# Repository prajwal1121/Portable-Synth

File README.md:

# Portable Synth
### An OP-1 inspired portable groovebox based around Teensy 4.1
Built using the awesome Teensy Audio Library
 
This project is still in progress, and will be for a while. Check back often for updates and bug fixes

**Current Status (1/13/2021)::white_check_mark:**

**Latest Updates (2/3/2021):** This code is outgrowing the Arduino IDE and I'm finally making the switch to VSCode and Platformio! This means the code will now and henceforth be organized in a more traditional C++ project structure rather than an awkward collections of .ino files. More importantly, the latest groovebox firmware has been reorganized into classes and multiple files in an effort to make it more modulualr and OOP-y. See README in Software folder for more information.

##### Check out the following links for development updates and more information about how to use the project files above
* Part 1 (Version 1): http://praj.tech/portfolio/portable-synth-v1-prototype/
* Part 2 (Version 1): http://praj.tech/portfolio/portable-synth-concept-design/
* Part 3 (Version 2): http://praj.tech/portfolio/porable-synth-hardware-upgrade/
* Part 4 (Version 2): http://praj.tech/portfolio/portable-synth-v2/

##### Or watch the demo videos here
###### V2
* Audio Recording and FM Radio: https://youtu.be/2ahzlKvuJ6E
* Build: https://youtu.be/Mdk-aUEtNno
* Sample Packs and Step Sequencer: https://youtu.be/XyqohSevqoo
* V2 Hardware and Synth with Mod Matrix: https://youtu.be/yj9AeDa9qw8

###### V1
* Endless Sequencer: https://youtu.be/U5Ci-TUZ0MY
* Recording and Sampling: https://youtu.be/KuPWz8McP5k
* Subtractive Synthesizer: https://youtu.be/QcZ3WIZ24l4

#### V2 - November 2020

#### V1 Prototype - August 2020

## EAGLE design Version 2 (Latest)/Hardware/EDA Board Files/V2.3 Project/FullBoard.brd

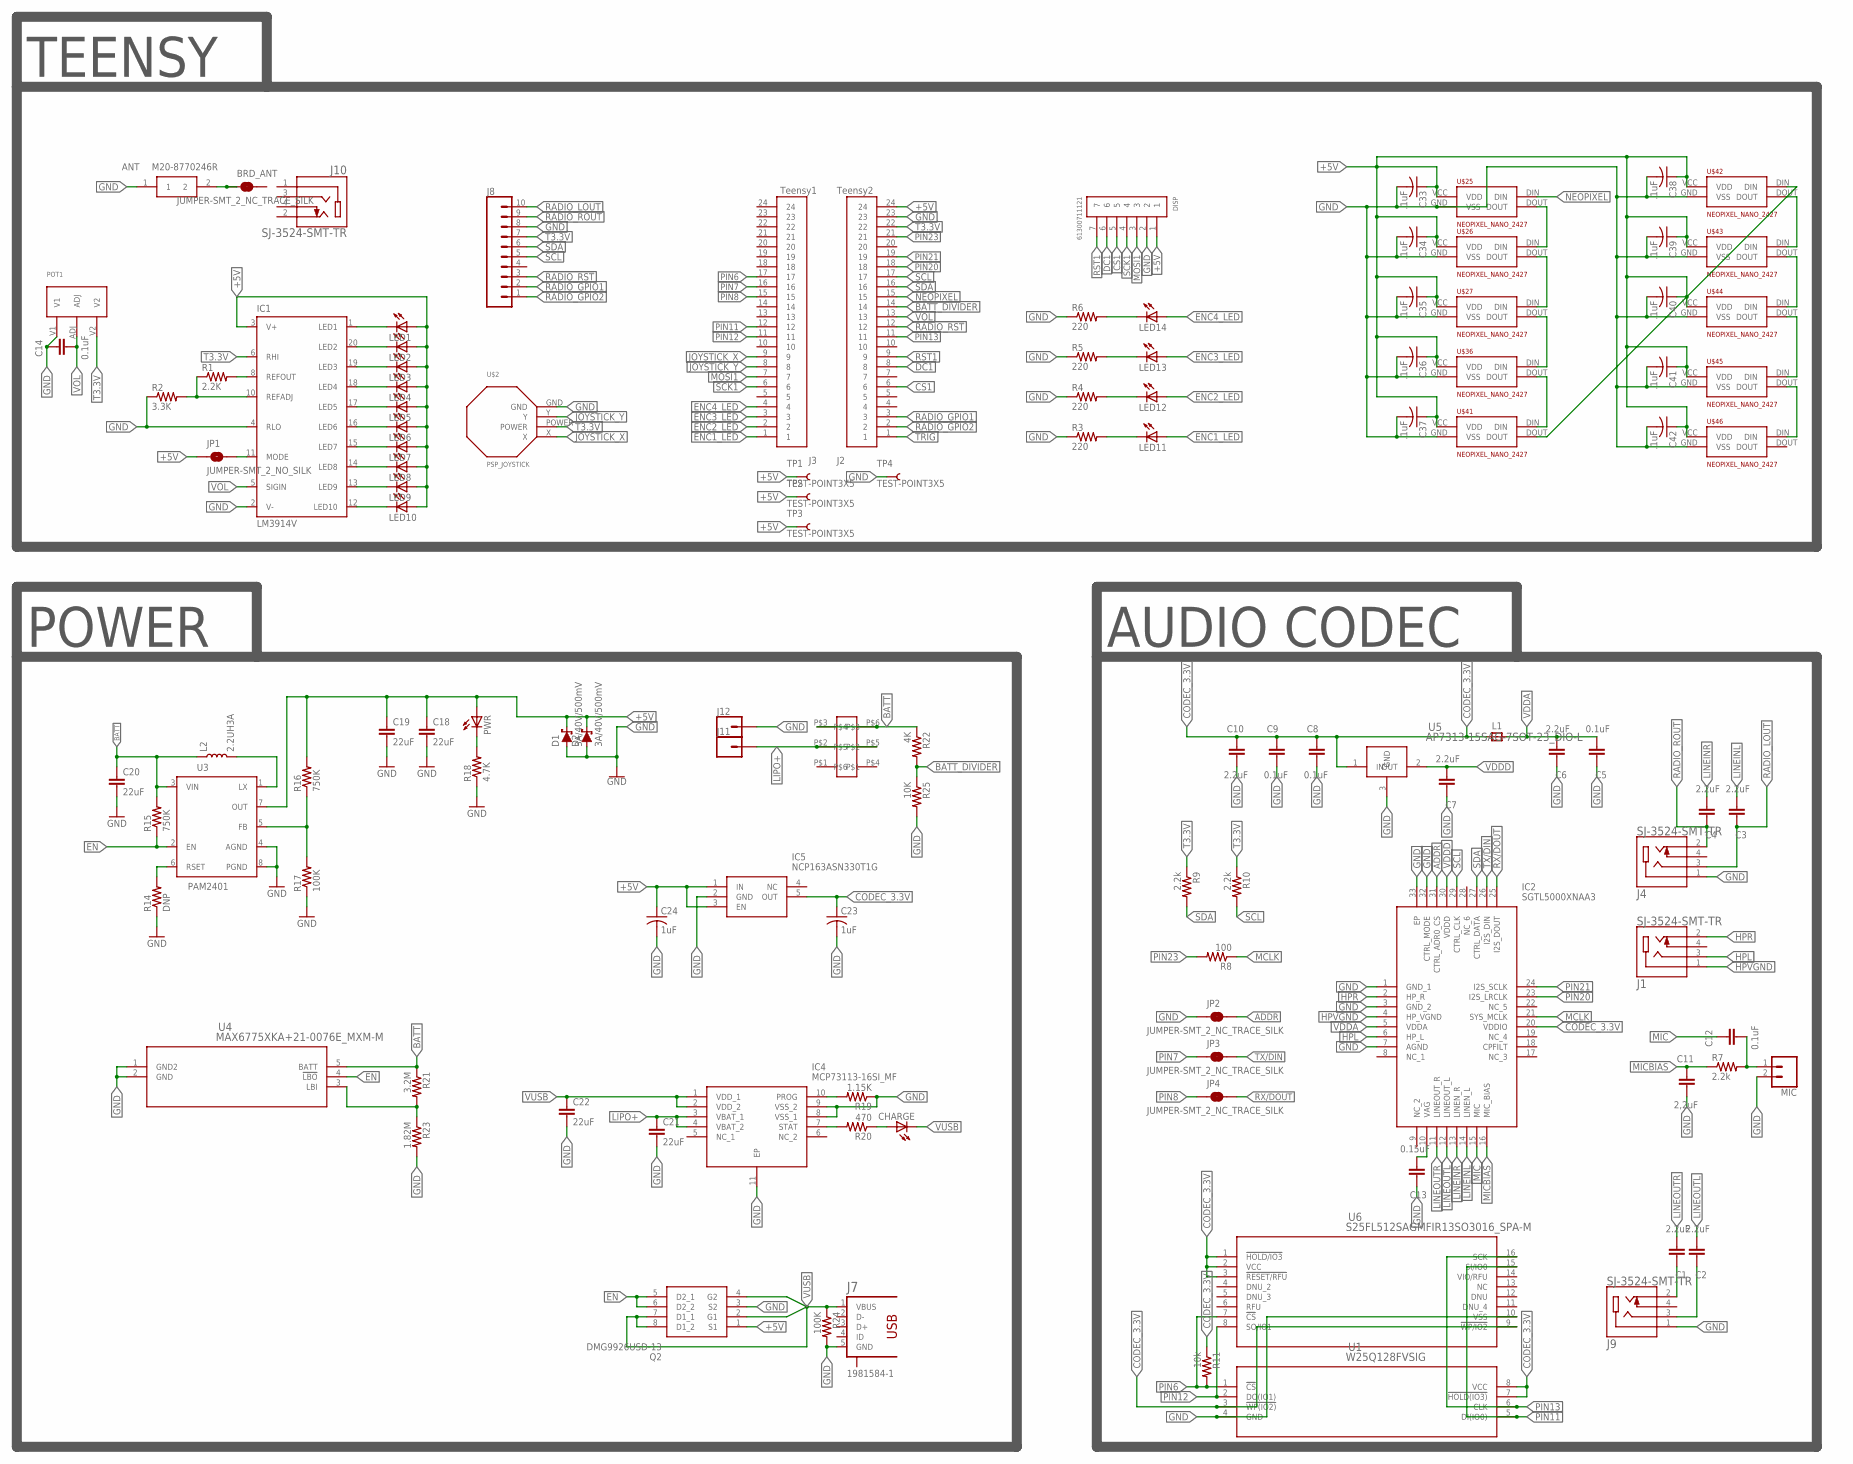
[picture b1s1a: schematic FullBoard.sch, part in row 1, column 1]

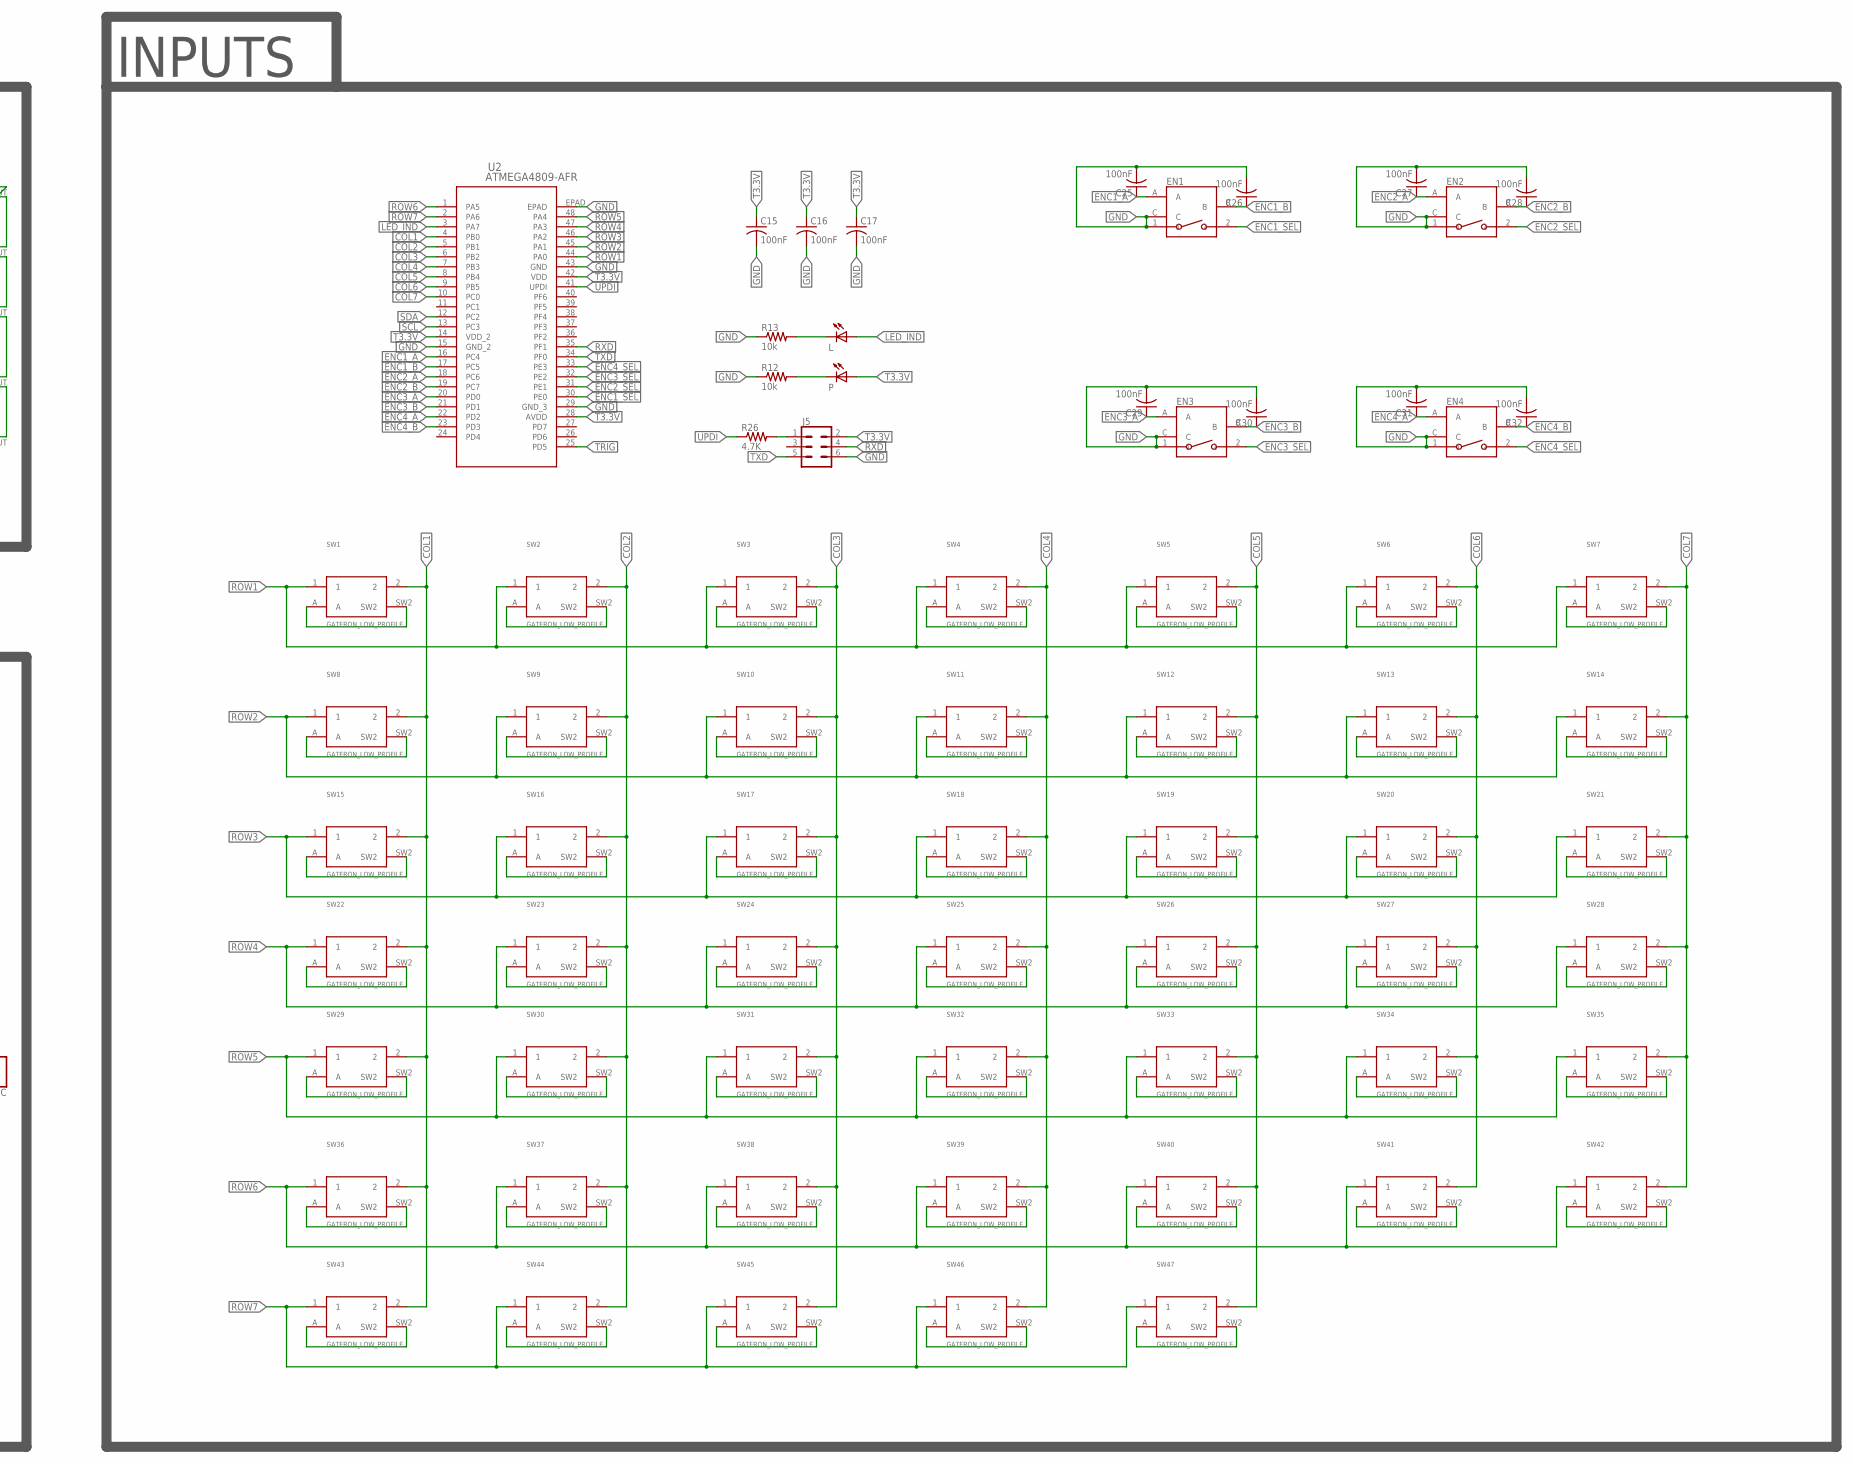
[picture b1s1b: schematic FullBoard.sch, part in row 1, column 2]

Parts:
ANT: M20-8770246R; M208770246R
BRD_ANT: JUMPER-SMT_2_NC_TRACE_SILK; SMT-JUMPER_2_NC_TRACE_SILK
C1, C2, C3, C4, C6, C7, C10: 2.2uF; CAP_0805
C5, C8, C9, C12, C14: 0.1uF; CAP_0805
C11: 2,2uF; CAP_0805
C13: 0.15uF; CAP_0805
C15, C16, C17, C25, C26, C27, C28, C29, C30, C31, C32: 100nF; C0805
C18, C19, C20, C21, C22: 22uF; 0805
C23, C24: 1uF; C1206
C33, C34, C35, C36, C37, C38, C39, C40, C41, C42: .1uF; C0805
CHARGE: LEDCHIPLED_0805; CHIPLED_0805
D1, D2: 3A/40V/500mV; SMA-DIODE
DISP: 61300711121
EN1, EN2, EN3, EN4: PEC11R-4215K-S0024
IC1: LM3914V; PLCC20S
IC2: SGTL5000XNAA3; QFN50P500X500X90-33N
IC4: MCP73113-16SI_MF; SON50P300X300X100-11N
IC5: NCP163ASN330T1G; SOT95P280X145-5N
J1, J4, J9, J10: SJ-3524-SMT-TR
J2: Teensy2; 61302411121
J3: Teensy1; 61302411121
J5: CONN_03X2FEMALE_SMD; 2X3_SMD
J7: 1981584-1
J8: CONN_10SMD_MALE; 1X10_SMD_MALE
J11, J12: CONN_01; 1X01
JP1: JUMPER-SMT_2_NO_SILK; SMT-JUMPER_2_NO_SILK
JP2, JP3, JP4: JUMPER-SMT_2_NC_TRACE_SILK; SMT-JUMPER_2_NC_TRACE_SILK
L: LEDCHIPLED_0805; CHIPLED_0805
L1: RC-MASTER-SMD_FB_0805MP; RC-MASTER-SMD_L0805MP
L2: 2.2UH3A; INDUCTOR_4X4MM
LED1, LED2, LED3, LED4, LED5, LED6, LED7, LED8, LED9, LED10: LEDCHIP-LED0805; CHIP-LED0805
LED11, LED12, LED13, LED14: LEDCHIPLED_0805; CHIPLED_0805
MIC: CONN_02; 1X02
P: LEDCHIPLED_0805; CHIPLED_0805
POT1: P0915N_POT; PO915N_POT
PWR: LEDCHIPLED_0805; CHIPLED_0805
Q2: DMG9926USD-13; SOIC127P600X175-8N
R1: 2.2K; M0805
R2: 3.3K; M0805
R3, R4, R5, R6: 220; R0805
R7, R9, R10: 2.2k; R0805
R8: 100; R0805
R11, R12, R13: 10k; R0805
R14: DNP; M0805
R15, R16: 750K; M0805
R17, R24: 100K; M0805
R18: 4.7K; M0805
R19: 1.15K; M0805
R20: 470; M0805
R21: 3.2M; M0805
R22: 4K; M0805
R23: 1.82M; M0805
R25: 10K; M0805
R26: 4.7K; R0805
SW1, SW2, SW3, SW4, SW5, SW6, SW7, SW8, SW9, SW10, SW11, SW12, SW13, SW14, SW15, SW16, SW17, SW18, SW19, SW20, SW21, SW22, SW23, SW24, SW25, SW26, SW27, SW28, SW29, SW30, SW31, SW32, SW33, SW34, SW35, SW36, SW37, SW38, SW39, SW40, SW41, SW42, SW43, SW44, SW45, SW46, SW47: GATERON_LOW_PROFILE; GATERON_LP_PLAIN
TP1, TP2, TP3, TP4: TEST-POINT3X5; PAD.03X.05
U1: W25Q128FVSIG; WIN_S-8_WIN
U2: ATMEGA4809-AFR; TQFP48_7X7MC_MCH
U3: PAM2401; MSOP8
U4: MAX6775XKA+21-0076E_MXM-M; 21-0076E_MXM-M
U5: AP7313-15SAG-7SOT-23_DIO-L; SOT-23_DIO-L
U6: S25FL512SAGMFIR13SO3016_SPA-M; SO3016_SPA-M
U$1: JS202011JAQN
U$2: PSP_JOYSTICK
U$25, U$26, U$27, U$36, U$41, U$42, U$43, U$44, U$45, U$46: NEOPIXEL_NANO_2427; SK6805-2427

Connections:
!RADIO_RST: J2.12, J8.3
+5V: C18.1, C19.1, C24.1, C33.1, C34.1, C35.1, C36.1, C37.1, C38.1, C39.1, C40.1, C41.1, C42.1, D1.C, D2.C, DISP.1, IC1.3 (V+), IC5.1 (IN), IC5.3 (EN), J2.24, JP1.1, LED1.A, LED2.A, LED3.A, LED4.A, LED5.A, LED6.A, LED7.A, LED8.A, LED9.A, LED10.A, PWR.A, Q2.1 (S1), R16.2, TP1.P$1, TP2.P$1, TP3.P$1, U3.7 (OUT), U$25.VCC (VDD), U$26.VCC (VDD), U$27.VCC (VDD), U$36.VCC (VDD), U$41.VCC (VDD), U$42.VCC (VDD), U$43.VCC (VDD), U$44.VCC (VDD), U$45.VCC (VDD), U$46.VCC (VDD)
ADDR: IC2.31 (CTRL_ADR0_CS), JP2.2
BATT: C20.1, L2.P$1 (1), R15.2, R21.1, R22.1, U3.3 (VIN), U4.5 (BATT), U$1.P$3, U$1.P$6
BATT_DIVIDER: J2.14, R22.2, R25.1
CODEC_3.3V: C8.1, C9.1, C10.1, C23.1, IC2.20 (VDDIO), IC5.5 (OUT), L1.1, R11.1, U1.3 (!WP(IO2)), U1.7 (!HOLD(IO3)), U1.8 (VCC), U5.1 (IN), U6.1 (!HOLD/IO3), U6.2 (VCC), U6.3 (!RESET/RFU), U6.9 (!WP/IO2)
COL1: SW1.2, SW8.2, SW15.2, SW22.2, SW29.2, SW36.2, SW43.2, U2.4 (PB0)
COL2: SW2.2, SW9.2, SW16.2, SW23.2, SW30.2, SW37.2, SW44.2, U2.5 (PB1)
COL3: SW3.2, SW10.2, SW17.2, SW24.2, SW31.2, SW38.2, SW45.2, U2.6 (PB2)
COL4: SW4.2, SW11.2, SW18.2, SW25.2, SW32.2, SW39.2, SW46.2, U2.7 (PB3)
COL5: SW5.2, SW12.2, SW19.2, SW26.2, SW33.2, SW40.2, SW47.2, U2.8 (PB4)
COL6: SW6.2, SW13.2, SW20.2, SW27.2, SW34.2, SW41.2, U2.9 (PB5)
COL7: SW7.2, SW14.2, SW21.2, SW28.2, SW35.2, SW42.2, U2.10 (PC0)
CS1: DISP.5, J2.6
DC1: DISP.6, J2.8
EN: Q2.5 (D2_1), Q2.6 (D2_2), R15.1, U3.2 (EN), U4.4 (!LBO)
ENC1_A: C25.1, EN1.A, U2.16 (PC4)
ENC1_B: C26.1, EN1.B, U2.17 (PC5)
ENC1_LED: J3.1, LED11.A
ENC1_SEL: EN1.2, U2.30 (PE0)
ENC2_A: C27.1, EN2.A, U2.18 (PC6)
ENC2_B: C28.1, EN2.B, U2.19 (PC7)
ENC2_LED: J3.2, LED12.A
ENC2_SEL: EN2.2, U2.31 (PE1)
ENC3_A: C29.1, EN3.A, U2.20 (PD0)
ENC3_B: C30.1, EN3.B, U2.21 (PD1)
ENC3_LED: J3.3, LED13.A
ENC3_SEL: EN3.2, U2.32 (PE2)
ENC4_A: C31.1, EN4.A, U2.22 (PD2)
ENC4_B: C32.1, EN4.B, U2.23 (PD3)
ENC4_LED: J3.4, LED14.A
ENC4_SEL: EN4.2, U2.33 (PE3)
GND: ANT.1, C5.1, C6.1, C7.1, C8.2, C9.2, C10.2, C11.2, C13.1, C14.1, C15.2, C16.2, C17.2, C18.2, C19.2, C20.2, C21.2, C22.2, C23.2, C24.2, C25.2, C26.2, C27.2, C28.2, C29.2, C30.2, C31.2, C32.2, C33.2, C34.2, C35.2, C36.2, C37.2, C38.2, C39.2, C40.2, C41.2, C42.2, D1.A, D2.A, DISP.2, EN1.1, EN1.C, EN2.1, EN2.C, EN3.1, EN3.C, EN4.1, EN4.C, IC1.2 (V-), IC1.4 (RLO), IC2.1 (GND_1), IC2.3 (GND_2), IC2.7 (AGND), IC2.32 (CTRL_MODE), IC2.33 (EP), IC4.8 (VSS_1), IC4.9 (VSS_2), IC4.11 (EP), IC5.2 (GND), J2.23, J4.1, J5.6, J7.5 (GND), J8.8, J9.1, J12.1, JP2.1, MIC.2, POT1.V1, Q2.3 (S2), R2.1, R3.1, R4.1, R5.1, R6.1, R12.1, R13.1, R14.1, R17.1, R18.1, R19.1, R23.2, R24.2, R25.2, TP4.P$1, U1.4 (GND), U2.15 (GND_2), U2.29 (GND_3), U2.43 (GND), U2.EPAD, U3.4 (AGND), U3.8 (PGND), U4.1 (GND2), U4.2 (GND), U5.3 (GND), U6.10 (VSS), U$2.GND, U$25.GND (VSS), U$26.GND (VSS), U$27.GND (VSS), U$36.GND (VSS), U$41.GND (VSS), U$42.GND (VSS), U$43.GND (VSS), U$44.GND (VSS), U$45.GND (VSS), U$46.GND (VSS)
HPL: IC2.6 (HP_L), J1.3
HPR: IC2.2 (HP_R), J1.2
HPVGND: IC2.4 (HP_VGND), J1.1
JOYSTICK_X: J3.9, U$2.X
JOYSTICK_Y: J3.8, U$2.Y
LED_IND: L.A, U2.3 (PA7)
LINEINL: C3.2, IC2.14 (LINEN_L)
LINEINR: C4.2, IC2.13 (LINEN_R)
LINEOUTL: C2.2, IC2.12 (LINEOUT_L)
LINEOUTR: C1.2, IC2.11 (LINEOUT_R)
LIPO+: C21.1, IC4.3 (VBAT_1), IC4.4 (VBAT_2), J11.1, U$1.P$2, U$1.P$5
MCLK: IC2.21 (SYS_MCLK), R8.1
MIC: C12.1, IC2.15 (MIC)
MICBIAS: C11.1, IC2.16 (MIC_BIAS), R7.1
MOSI1: DISP.3, J3.7
unnamed: IC1.18 (LED4), LED4.C
unnamed: IC1.1 (LED1), LED1.C
unnamed: IC1.20 (LED2), LED2.C
unnamed: IC1.19 (LED3), LED3.C
unnamed: SW1.A, SW1.SW2
unnamed: IC1.17 (LED5), LED5.C
unnamed: IC1.16 (LED6), LED6.C
unnamed: IC1.15 (LED7), LED7.C
unnamed: IC1.14 (LED8), LED8.C
unnamed: IC1.13 (LED9), LED9.C
unnamed: IC1.12 (LED10), LED10.C
unnamed: IC1.10 (REFADJ), R1.1, R2.2
unnamed: IC1.11 (MODE), JP1.2
unnamed: IC1.8 (REFOUT), R1.2
unnamed: LED12.C, R4.2
unnamed: LED14.C, R6.2
unnamed: LED13.C, R5.2
unnamed: C13.2, IC2.10 (VAG)
unnamed: C12.2, MIC.1, R7.2
unnamed: C1.1, J9.2
unnamed: C2.1, J9.3
unnamed: SW2.A, SW2.SW2
unnamed: SW3.A, SW3.SW2
unnamed: SW4.A, SW4.SW2
unnamed: SW5.A, SW5.SW2
unnamed: SW6.A, SW6.SW2
unnamed: SW7.A, SW7.SW2
unnamed: SW8.A, SW8.SW2
unnamed: SW9.A, SW9.SW2
unnamed: SW10.A, SW10.SW2
unnamed: SW11.A, SW11.SW2
unnamed: SW12.A, SW12.SW2
unnamed: SW13.A, SW13.SW2
unnamed: SW14.A, SW14.SW2
unnamed: SW15.A, SW15.SW2
unnamed: SW16.A, SW16.SW2
unnamed: SW17.A, SW17.SW2
unnamed: SW18.A, SW18.SW2
unnamed: SW19.A, SW19.SW2
unnamed: SW20.A, SW20.SW2
unnamed: SW21.A, SW21.SW2
unnamed: SW22.A, SW22.SW2
unnamed: SW23.A, SW23.SW2
unnamed: SW24.A, SW24.SW2
unnamed: SW25.A, SW25.SW2
unnamed: SW26.A, SW26.SW2
unnamed: SW27.A, SW27.SW2
unnamed: SW28.A, SW28.SW2
unnamed: SW29.A, SW29.SW2
unnamed: SW30.A, SW30.SW2
unnamed: SW31.A, SW31.SW2
unnamed: SW32.A, SW32.SW2
unnamed: SW33.A, SW33.SW2
unnamed: SW34.A, SW34.SW2
unnamed: SW35.A, SW35.SW2
unnamed: SW36.A, SW36.SW2
unnamed: SW37.A, SW37.SW2
unnamed: SW38.A, SW38.SW2
unnamed: SW39.A, SW39.SW2
unnamed: SW40.A, SW40.SW2
unnamed: SW41.A, SW41.SW2
unnamed: SW42.A, SW42.SW2
unnamed: SW43.A, SW43.SW2
unnamed: SW44.A, SW44.SW2
unnamed: SW45.A, SW45.SW2
unnamed: SW46.A, SW46.SW2
unnamed: SW47.A, SW47.SW2
unnamed: L.C, R13.2
unnamed: P.C, R12.2
unnamed: LED11.C, R3.2
unnamed: R16.1, R17.2, U3.5 (FB)
unnamed: L2.P$2 (2), U3.1 (LX)
unnamed: R14.2, U3.6 (RSET)
unnamed: PWR.C, R18.2
unnamed: IC4.10 (PROG), R19.2
unnamed: IC4.7 (STAT), R20.2
unnamed: CHARGE.A, R20.1
unnamed: R21.2, R23.1, U4.3 (LBI)
unnamed: U$25.DOUT, U$26.DIN
unnamed: U$26.DOUT, U$27.DIN
unnamed: U$27.DOUT, U$36.DIN
unnamed: U$36.DOUT, U$41.DIN
unnamed: U$41.DOUT, U$42.DIN
unnamed: U$42.DOUT, U$43.DIN
unnamed: U$43.DOUT, U$44.DIN
unnamed: U$44.DOUT, U$45.DIN
unnamed: U$45.DOUT, U$46.DIN
unnamed: ANT.2, BRD_ANT.1
unnamed: J5.1, R26.2
NEOPIXEL: J2.15, U$25.DIN
PIN6: J3.17, R11.2, U1.1 (!CS), U6.7 (!CS)
PIN7: J3.16, JP3.1
PIN8: J3.15, JP4.1
PIN11: J3.12, U1.5 (DI(IO0)), U6.15 (SI/IO0)
PIN12: J3.11, U1.2 (DO(IO1)), U6.8 (SO/IO1)
PIN13: J2.11, U1.6 (CLK), U6.16 (SCK)
PIN20: IC2.23 (I2S_LRCLK), J2.18
PIN21: IC2.24 (I2S_SCLK), J2.19
PIN23: J2.21, R8.2
RADIO_GPIO1: J2.3, J8.2
RADIO_GPIO2: J2.2, J8.1
RADIO_LOUT: C3.1, J4.3, J8.10
RADIO_ROUT: C4.1, J4.2, J8.9
ROW1: SW1.1, SW2.1, SW3.1, SW4.1, SW5.1, SW6.1, SW7.1, U2.44 (PA0)
ROW2: SW8.1, SW9.1, SW10.1, SW11.1, SW12.1, SW13.1, SW14.1, U2.45 (PA1)
ROW3: SW15.1, SW16.1, SW17.1, SW18.1, SW19.1, SW20.1, SW21.1, U2.46 (PA2)
ROW4: SW22.1, SW23.1, SW24.1, SW25.1, SW26.1, SW27.1, SW28.1, U2.47 (PA3)
ROW5: SW29.1, SW30.1, SW31.1, SW32.1, SW33.1, SW34.1, SW35.1, U2.48 (PA4)
ROW6: SW36.1, SW37.1, SW38.1, SW39.1, SW40.1, SW41.1, SW42.1, U2.1 (PA5)
ROW7: SW43.1, SW44.1, SW45.1, SW46.1, SW47.1, U2.2 (PA6)
RST1: DISP.7, J2.9
RX/DOUT: IC2.25 (I2S_DOUT), JP4.2
RXD: J5.4, U2.35 (PF1)
SCK1: DISP.4, J3.6
SCL: IC2.29 (CTRL_CLK), J2.17, J8.5, R10.2, U2.13 (PC3)
SDA: IC2.27 (CTRL_DATA), J2.16, J8.6, R9.2, U2.12 (PC2)
T3.3V: C15.1, C16.1, C17.1, IC1.6 (RHI), J2.22, J5.2, J8.7, P.A, POT1.V2, R9.1, R10.1, U2.14 (VDD_2), U2.28 (AVDD), U2.42 (VDD), U$2.POWER
TRIG: J2.1, U2.25 (PD5)
TX/DIN: IC2.26 (I2S_DIN), JP3.2
TXD: J5.5, U2.34 (PF0)
UPDI: R26.1, U2.41 (UPDI)
VDDA: C5.2, C6.2, IC2.5 (VDDA), L1.2
VDDD: C7.2, IC2.30 (VDDD), U5.2 (OUT)
VOL: C14.2, IC1.5 (SIGIN), J2.13, POT1.ADJ
VUSB: C22.1, CHARGE.C, IC4.1 (VDD_1), IC4.2 (VDD_2), J7.1 (VBUS), Q2.2 (G1), Q2.4 (G2), Q2.7 (D1_1), Q2.8 (D1_2), R24.1

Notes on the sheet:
POWER
AUDIO CODEC
TEENSY
INPUTS

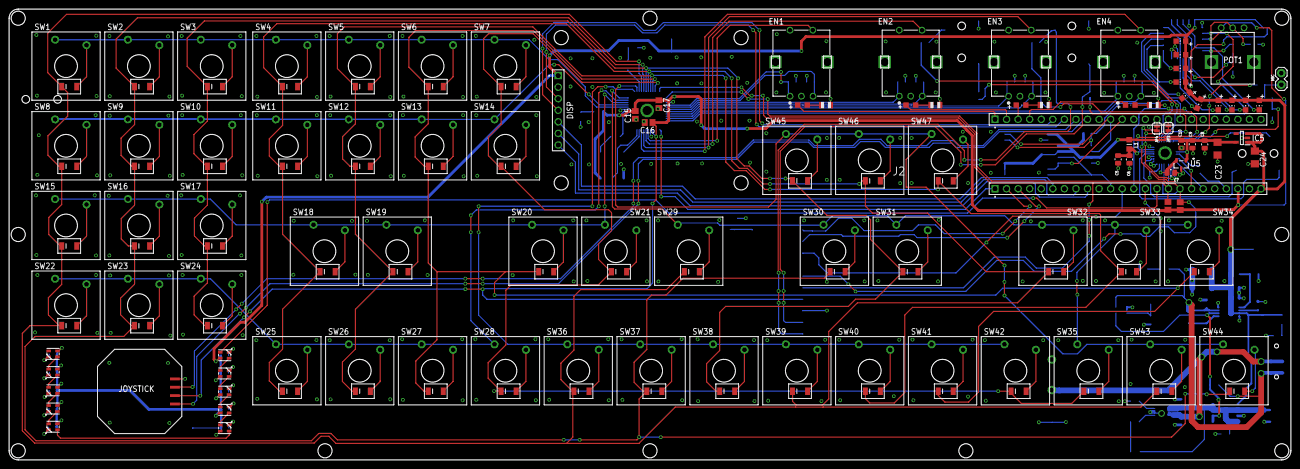
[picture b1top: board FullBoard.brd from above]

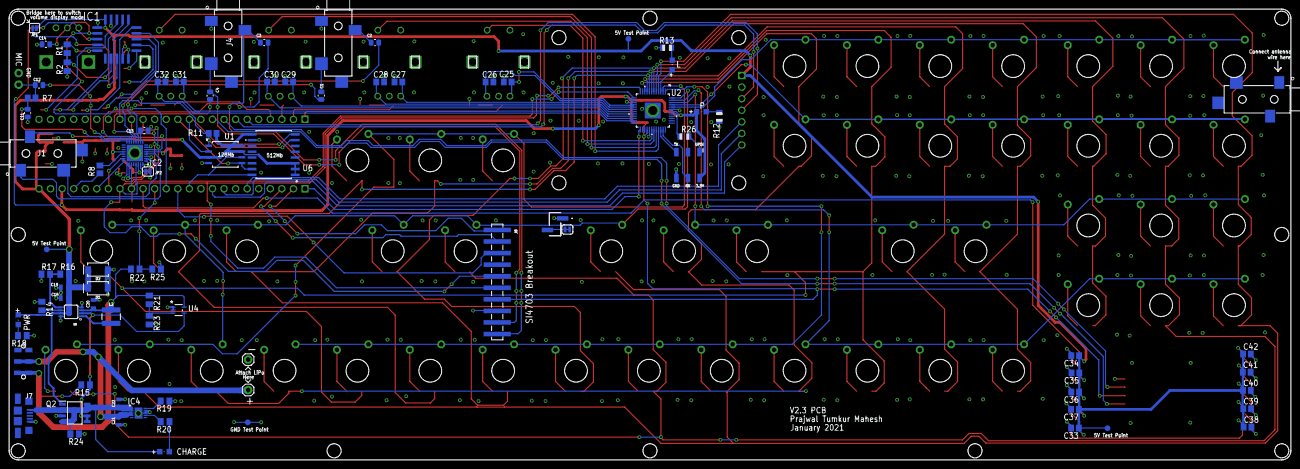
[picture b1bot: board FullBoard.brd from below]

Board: 4 copper layers, 281.5 x 99.0 mm, 188 parts (85 on the bottom side), 173 nets.

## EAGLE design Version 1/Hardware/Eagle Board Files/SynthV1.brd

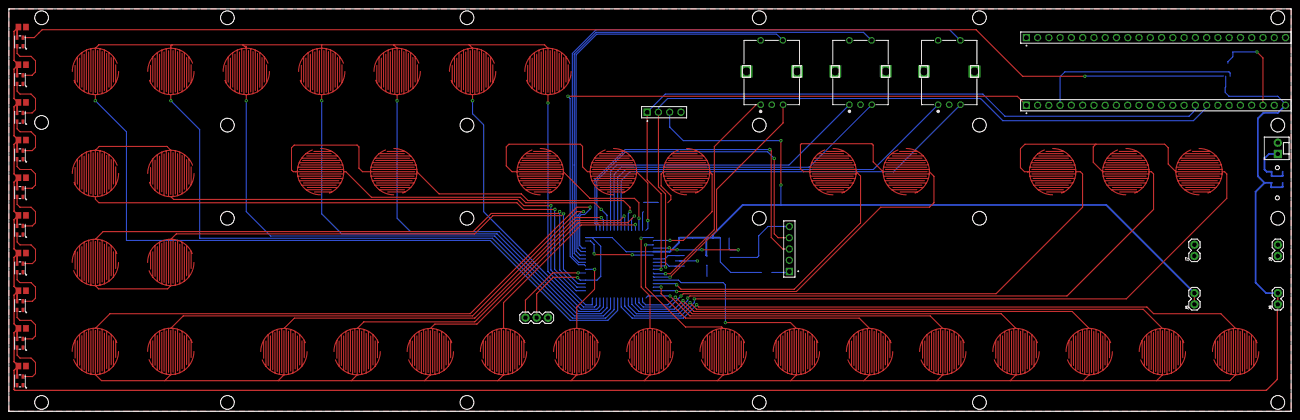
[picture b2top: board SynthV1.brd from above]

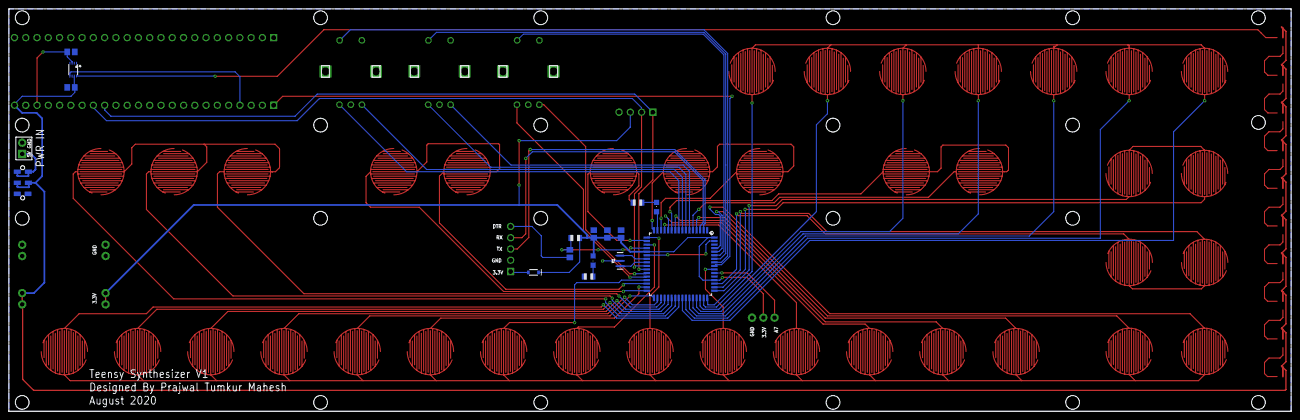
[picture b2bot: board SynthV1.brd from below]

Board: 2 copper layers, 289.0 x 90.7 mm, 86 parts (16 on the bottom side), 76 nets.

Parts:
38: BUTTONPAD
A7: 1X03
C1, C2, C3, C4, C5, C6, C7, C8, C9, C10, C11, C12, C13, C14, C15, C16: .1uF; C0805
D1: 0.5A/40V/420mV; SOD-323
EN1, EN2, EN3: PEC11R-4215K-S0024
J1: 61300511121
J2: Teensy2; 61302411121
J3: Teensy1; 61302411121
J4: OLED; 61300411121
J5, J7, J8, J9: 1X02
J6: MOLEX-1X2
LED1, LED2: CHIPLED_0805
R1, R2, R3: 10k; R0805
U1: ATMEGA64A-AU; QFP80P1600X1600X120-64N
U2: VFSOP-8
U$1, U$2, U$3, U$4, U$5, U$6, U$7, U$8, U$9, U$10, U$11, U$12, U$13, U$14, U$15, U$16, U$17, U$18, U$19, U$20, U$21, U$22, U$23, U$24, U$28, U$29, U$30, U$31, U$32, U$33, U$34, U$35, U$37, U$38, U$39, U$40: BUTTONPAD
U$25, U$26, U$27, U$36, U$41, U$42, U$43, U$44, U$45, U$46: NEOPIXEL_NANO_2427; SK6805-2427
U$47: JS202011JAQN
Y1: 8MHz; RESONATOR-SMD-3.2X1.3

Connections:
2: U1.4, U$1.P$2
3: U1.5, U$15.P$2
3.3V: A7.2, C1.1, C2.1, C3.1, D1.C, J4.3, J5.1, J5.2, LED1.A, R3.1, U1.21, U1.52, U1.64
5V: C5.1, C7.1, C8.1, C9.1, C10.1, C11.1, C12.1, C13.1, C14.1, C15.1, C16.1, J2.24, J8.1, J8.2, U2.P$7, U$25.VCC, U$26.VCC, U$27.VCC, U$36.VCC, U$41.VCC, U$42.VCC, U$43.VCC, U$44.VCC, U$45.VCC, U$46.VCC, U$47.P$2, U$47.P$5
5VIN: J6.1, U$47.P$3, U$47.P$6
8: U1.10, U$2.P$2
9: U1.11, U$16.P$2
10: U1.12, U$3.P$2
11: U1.13, U$4.P$2
12: U1.14, U$17.P$2
13: LED2.A, U1.15
14: U1.16, U$18.P$2
15: U1.17, U$6.P$2
16: U1.18, U$19.P$2
17: U1.19, U$7.P$2
22: U1.29, U$8.P$2
23: U1.30, U$20.P$2
24: U1.31, U$9.P$2
25: U1.32, U$21.P$2
26: U1.33, U$10.P$2
27: U1.34, U$11.P$2
28: U1.35, U$22.P$2
29: U1.36, U$12.P$2
30: U1.37, U$23.P$2
31: U1.38, U$13.P$2
32: U1.39, U$24.P$2
33: U1.40, U$14.P$2
34: U1.41, U$37.P$2
35: U1.42, U$38.P$2
36: U1.43, U$39.P$2
37: U1.44, U$40.P$2
38: 38.P$2, U1.45
39: U1.46, U$35.P$2
40: U1.47, U$34.P$2
41: U1.48, U$33.P$2
42: U1.49, U$29.P$2
43: U1.50, U$30.P$2
44: U1.51, U$31.P$2
A0: U1.61, U$32.P$2
A1: U1.60, U$28.P$2
A2: EN1.2, U1.59
A3: EN2.2, U1.58
A4: EN3.2, U1.57
A5: J2.1, U1.56
A6: U1.55, U$5.P$2
A7: A7.3, U1.54
DTR: C4.2, J1.5
GND: 38.P$1, A7.1, C1.2, C2.2, C3.2, C5.2, C6.2, C7.2, C8.2, C9.2, C10.2, C11.2, C12.2, C13.2, C14.2, C15.2, C16.2, EN1.1, EN1.C, EN2.1, EN2.C, EN3.1, EN3.C, J1.2, J2.23, J4.4, J6.2, J7.1, J7.2, J9.1, J9.2, R1.1, R2.1, U1.22, U1.53, U1.63, U2.P$2, U$1.P$1, U$2.P$1, U$3.P$1, U$4.P$1, U$5.P$1, U$6.P$1, U$7.P$1, U$8.P$1, U$9.P$1, U$10.P$1, U$11.P$1, U$12.P$1, U$13.P$1, U$14.P$1, U$15.P$1, U$16.P$1, U$17.P$1, U$18.P$1, U$19.P$1, U$20.P$1, U$21.P$1, U$22.P$1, U$23.P$1, U$24.P$1, U$25.GND, U$26.GND, U$27.GND, U$28.P$1, U$29.P$1, U$30.P$1, U$31.P$1, U$32.P$1, U$33.P$1, U$34.P$1, U$35.P$1, U$36.GND, U$37.P$1, U$38.P$1, U$39.P$1, U$40.P$1, U$41.GND, U$42.GND, U$43.GND, U$44.GND, U$45.GND, U$46.GND, Y1.2
INT0: EN1.A, U1.27
INT1: EN1.B, U1.28
INT2: EN2.A, U1.6
INT3: EN2.B, U1.7
INT4: EN3.A, U1.8
INT5: EN3.B, U1.9
LED_H: U2.P$8, U$25.DIN
LED_L: J2.4, U2.P$5
unnamed: U1.23, Y1.3
unnamed: U$25.DOUT, U$26.DIN
unnamed: U$26.DOUT, U$27.DIN
unnamed: U$27.DOUT, U$36.DIN
unnamed: U$36.DOUT, U$41.DIN
unnamed: U$41.DOUT, U$42.DIN
unnamed: U$42.DOUT, U$43.DIN
unnamed: U$43.DOUT, U$44.DIN
unnamed: U$44.DOUT, U$45.DIN
unnamed: LED2.C, R2.2
unnamed: LED1.C, R1.2
unnamed: U$45.DOUT, U$46.DIN
RST: C4.1, R3.2, U1.20
RX0: J1.3, U1.2
SCL: J2.17, J4.2, U1.25
SDA: J2.16, J4.1, U1.26
T3.3V: C6.1, J2.22, U2.P$3
TX0: J1.4, U1.3
VUSB: D1.A, J1.1
XTAL1: U1.24, Y1.1

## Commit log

2020-08-25 Github upload
2020-08-26 Added metronome
2020-08-26 Added keyboard gain control
2020-08-31 Synth upload
2020-09-02 Added ASDT export and removed unused connections
2020-10-25 Added modified playSDRaw files for Audio Library
2020-11-25 Updating README for incoming V2 stuff
2020-11-25 Added V1 CAD and restructured files
2020-12-07 V2 Subtractive Synth
2020-12-20 Added V2 CAD and EDA files
2020-12-29 Added combined system code
2020-12-30 Added modified Audio Library files
2021-01-14 Added V2.3 Files and BOM
2021-01-14 Added STL files for easier 3D printing
2021-01-14 Added PJRC stuff to BOM
2021-01-20 Added Audio Recorder Code
2021-01-21 Moved a few vars to PROGMEM
2021-02-04 Merged recorder code into main project and shifted to Platformio
2021-02-04 Added firmware hex folder
2021-02-06 Updated battery connector on PCB

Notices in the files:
parts and their libraries:
SparkFun-Clocks: Licensing: Creative Commons ShareAlike 4.0 International - https://creativecommons.org/licenses/by-sa/4.0
SparkFun-Capacitors: Licensing: CC v3.0 Share-Alike You are welcome to use this library for commercial purposes.
